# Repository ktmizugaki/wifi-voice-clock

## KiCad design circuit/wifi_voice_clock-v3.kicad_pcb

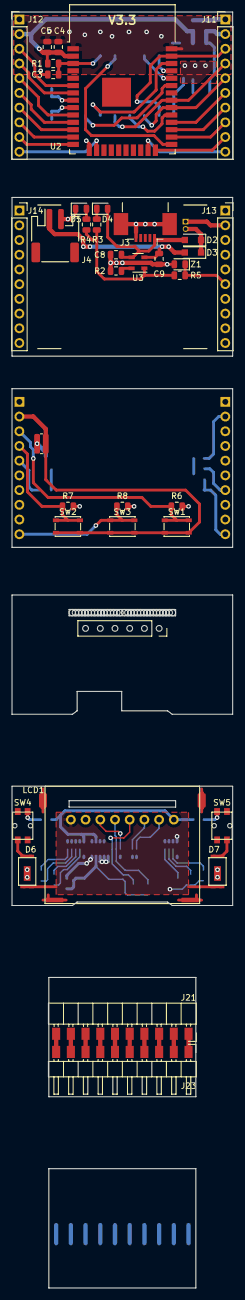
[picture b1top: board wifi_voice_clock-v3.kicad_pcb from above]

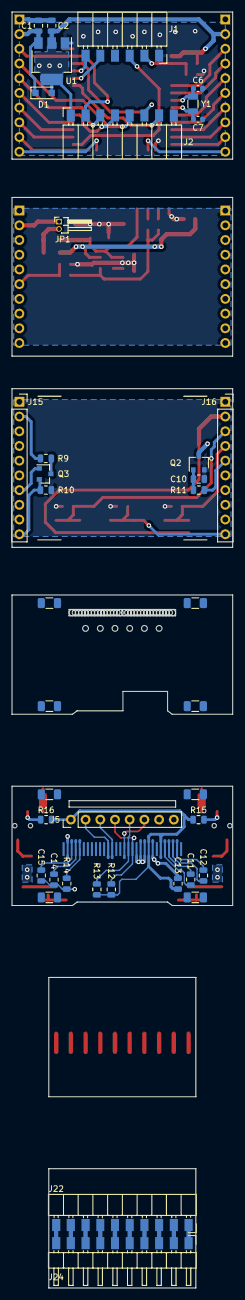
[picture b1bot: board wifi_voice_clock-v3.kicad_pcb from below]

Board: 2 copper layers, 38.1 x 220.3 mm, 68 parts (31 on the bottom side), 88 nets.

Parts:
C1, C2, C10, C11, C12, C13: 1uF; C_0805_2012Metric
C3, C4: 0.1uF; C_0805_2012Metric
C5, C8, C9: 10uF; C_0805_2012Metric
C6, C7: 15pF; C_0603_1608Metric
C14: 4.7uF; C_0805_2012Metric
C15: 2.2uF; C_0805_2012Metric
D1, D2: GS1010FL; D_SOD-123F
D3: SS2040FL; D_SOD-123F
D4: Orange; LED_0805_2012Metric
D5: Grean; LED_0805_2012Metric
D6, D7: SPMWHT541MD5WAR0SD; LM561B
J1: PinSocket 1x06 5.7mm; PinSocket_1x06_P2.54mm_5.7mm_Horizontal_SMD
J2: PinSocket 1x08 5.7mm; PinSocket_1x08_P2.54mm_5.7mm_Horizontal_SMD
J3: USB_B_Mini; USB_Mini-B_Hirose_UX60SC-MB-5ST
J4: BATTERY; JST_PH_S2B-PH-SM4-TB_1x02-1MP_P2.00mm_Horizontal
J5: PinHeader 1x08 7.7mm; PinHeader_1x08_P2.54mm_Vertical
J11, J12: PinHeader 1x10 7.7mm; PinHeader_1x10_P2.54mm_Vertical
J13, J14, J15, J16: PinSocket 1x10 3.5mm; PinSocket_1x10_P2.54mm_Vertical
J21, J22: PinSocket 1x10 3.5mm; PinSocket_1x10_P2.54mm_3.5mm_Horizontal_SMD
J23, J24: PinHeader 1x10 3mm; PinHeader_1x10_P2.54mm_3mm_Horizontal_SMD
JP1: Jumper; PinHeader_1x02_P1.27mm_Horizontal
LCD1: ER-OLED0.96; OLED0.96
LS1: CES-20134-088PM; R_0612_1632Metric
Q2: 2SC3265-Y; SC-59
Q3: BSS138; SOT-23
R1, R2, R5, R6, R7, R8, R10, R12, R13: 10K; R_0805_2012Metric
R3, R4: 470; R_0805_2012Metric
R9: 40K; R_0805_2012Metric
R11: 820; R_0805_2012Metric
R14: 910K; R_0805_2012Metric
R15, R16: 1K; R_0805_2012Metric
SW1, SW2, SW3: SW_Push; SW_SPST_PTS810
SW4, SW5: THAU13
U1: ADP3338AKCZ-3.3; SOT-223-3_TabPin2
U2: ESP32-WROOM-32D; ESP32-WROOM-32
U3: MCP73831-2-OT; SOT-23-5
Y1: FC-135; Crystal_SMD_3215-2Pin_3.2x1.5mm
Z1: 3.3V; D_0805_2012Metric

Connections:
+3V3: C2.1, C4.2, C5.2, D1.2, J2.1, J12.2, R1.2, U1.2, U2.2
+5V: C8.1, D2.2, D4.2, J3.1, U3.4
+BATT: C9.2, D3.2, J4.1, U3.3
/CHGR_GND: C8.2, C9.1, D5.1, J3.5, J3.6, J4.2, J13.1, J14.1, R2.1, U3.2, Z1.2
/CHGR_STAT: J13.6, R5.2, Z1.1
/CHGR_VCC: J13.2, JP1.1
/CPU_EN: C3.1, J1.2, R1.1, U2.3
/CPU_IO0: J1.3, U2.25
/CPU_IO2: J11.9, U2.24
/CPU_IO4: J11.8, U2.26
/CPU_IO12: J12.9, U2.14
/CPU_IO13: J12.10, U2.16
/CPU_IO14: J12.8, U2.13
/CPU_IO15: J11.10, U2.23
/CPU_IO16: J11.7, U2.27
/CPU_IO17: J11.6, U2.28
/CPU_IO27: J12.7, U2.12
/CPU_RXD0: J1.5, U2.34
/CPU_SPK: J12.5, U2.10
/CPU_SPK2: J12.6, U2.11
/CPU_SW1: J12.3, U2.6
/CPU_SW2: J12.4, U2.7
/CPU_TXD0: J1.6, U2.35
/CPU_VSPICLK: J2.3, J11.5, U2.30
/CPU_VSPICS0: J2.4, U2.29
/CPU_VSPID: J2.2, J11.3, U2.37
/CPU_VSPIHD: J2.7, U2.33
/CPU_VSPIQ: J2.5, J11.4, U2.31
/CPU_VSPIWP: J2.6, U2.36
/CTRL_3V3: J16.2, LS1.1, SW1.2, SW2.2, SW3.2
/CTRL_GND: C10.2, J15.1, J16.1, Q2.2, R6.1, R7.1, R8.1, R10.1
/CTRL_SPK: J16.5, R11.2
/CTRL_SW1: J16.3, R6.2, SW1.1
/CTRL_SW2: J16.4, R7.2, SW2.1
/CTRL_SW3: J16.10, R8.2, SW3.1
/CTRL_VCC: J15.2, R9.2
/CTRL_VMES: J15.10, Q3.2, R10.2
/CTRL_VOUT: J15.7, Q3.1
/LCD_3V3: C13.2, J5.1, LCD1.6, LCD1.9, R12.2, R13.2, R15.2, R16.2
/LCD_GND: C13.1, C14.2, C15.2, D6.1, D7.1, J5.8, LCD1.8, LCD1.10, LCD1.11, LCD1.12, LCD1.29, R14.2
/LCD_LCDRS: J5.6, LCD1.15
/LCD_SCLK: J5.3, LCD1.18
/LCD_SDI: J5.2, LCD1.19
/MCP73831_STAT: R3.1, R4.1, R5.1, U3.1
/~LCD_LCDCS: J5.4, LCD1.13, R12.1
/~LCD_LCDRST: J5.5, LCD1.14, R13.1
GND: C1.2, C2.2, C3.2, C4.1, C5.1, C6.1, C7.1, J1.1, J2.8, J11.1, J12.1, U1.1, U2.1, U2.15, U2.38
unnamed: C6.2, U2.8, Y1.1
unnamed: C7.2, U2.9, Y1.2
unnamed: C10.1, Q2.1, R11.1
unnamed: C11.1, LCD1.4
unnamed: C11.2, LCD1.5
unnamed: C12.1, LCD1.2
unnamed: C12.2, LCD1.3
unnamed: C14.1, LCD1.27
unnamed: C15.1, LCD1.28
unnamed: D2.1, D3.1, JP1.2
unnamed: D4.1, R3.2
unnamed: D5.2, R4.2
unnamed: D6.2, SW4.1
unnamed: D7.2, SW5.1
unnamed: J21.1, J23.1
unnamed: J21.2, J23.2
unnamed: J21.3, J23.3
unnamed: J21.4, J23.4
unnamed: J21.5, J23.5
unnamed: J21.6, J23.6
unnamed: J21.7, J23.7
unnamed: J21.8, J23.8
unnamed: J21.9, J23.9
unnamed: J21.10, J23.10
unnamed: J22.1, J24.1
unnamed: J22.2, J24.2
unnamed: J22.3, J24.3
unnamed: J22.4, J24.4
unnamed: J22.5, J24.5
unnamed: J22.6, J24.6
unnamed: J22.7, J24.7
unnamed: J22.8, J24.8
unnamed: J22.9, J24.9
unnamed: J22.10, J24.10
unnamed: LCD1.26, R14.1
unnamed: LS1.2, Q2.3
unnamed: Q3.3, R9.1
unnamed: R2.2, U3.5
unnamed: R15.1, SW4.2
unnamed: R16.1, SW5.2
VCC: C1.1, D1.1, J11.2, U1.3

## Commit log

2021-07-06 Add circuit and gerver
2021-07-07 Add prog skelton
2021-07-14 Encrypto nvs with pre generated key
2021-07-26 Add simple_wifi
2021-07-26 Add json_str
2021-07-26 stub http_wifi_conf
2021-07-26 Add kurukuru
2021-07-26 Add connect to wifi conf
2021-07-26 Add http_html_cmn
2021-07-26 Implement handle_initial
2021-07-26 Implement http_wifi_conf
2021-07-26 Try mobile friendly
2021-07-26 Add "Uploaded files and code to GitHub" log
2021-07-31 Fix password in simple_wifi
2021-07-31 Fix wifi conf does not check valid
2021-08-02 Change prefix of SSID
2021-08-09 Fix project name in cmake build
2021-08-28 Update instractions in hackaday
2021-08-30 Add lock to simple_wifi
2021-08-30 Add simple wifi event
2021-08-30 Add "OLED worked! at least once" log
2021-09-05 Add alarm conf
2021-09-14 Add switches
2021-09-17 Add clock and sync with ntp
2021-09-17 Add lan manager
    - Add function to connect to wifi using wifi_conf
    - Add function to get mode of simple_wifi
2021-09-20 Fix http_wifi_conf
2021-10-03 Move gen outside of Makefile
2021-10-03 compile only relevant sources
2021-10-03 Fix cmake build
2021-10-03 Introduce event based loop
2021-10-03 Add display and graphics
2021-10-03 Add display clock
2021-10-03 Show SSID and password
2021-10-03 Add font/lang tools
2021-10-03 Add bitmap and text
2021-10-03 Add ssd1306 driver
2021-10-03 Add shinonome fonts
2021-10-03 Use shinonome to display texts
2021-10-03 Rework wifi_conf
2021-10-06 Add power management and wakeup timer
2021-10-07 Add vcc
2021-10-09 Use cmn.api
2021-10-09 Add clock conf
2021-10-09 Add index html
    Also handle SIGPIPE in test http server. changing page sometimes cause this signal.
2021-10-14 Add suspend mode
2021-10-14 Implement auto sync
2021-10-16 Send vcc to syslog server
2021-10-16 Add use 32KHz crystal settings to defaults
    It is needed to flash bootloader with this config
2021-10-16 Add audio component
2021-10-23 Implement play alarm
    Also increase max alarm sound.
2021-10-23 Add "Implemented display" log
2021-10-24 Add spiffs
2021-10-24 Implement say time
2021-10-25 Check battery level before starting wifi
2021-11-07 Improve json_str document
2021-11-10 Document clock
2021-11-11 Document switches
2021-11-14 Document alarm
2021-11-14 Document wifi conf
2021-11-14 Document simple wifi
2021-11-20 Measure real input voltage
    Circuit is from https://jeelabs.org/2013/05/17/zero-powe-battery-measurement/
2021-11-23 Add "Add alarm functionality" log
2021-12-05 Add tests for cmn.js
    Using Mocha.js with Chai.js.
2021-12-05 Update http_html_cmn
    - Make send error json cmn
    - Decode urlencoded parameters in query parse.
    - Attempt to support larger body using less memory in query parse.
2021-12-05 Implement update firmware
2021-12-05 Implement update spiffs
2021-12-05 Add http_firmware
2021-12-05 Disable print time for release build
2021-12-12 Change hostname used in DHCP request
2021-12-19 Add callbacks to firmware update
2021-12-26 Show date by right button
2021-12-26 Add "Firmware update" log
2022-03-08 Swap function of middle click and middle long
2022-03-08 Show battery level on clock
2022-03-17 Implement listview and menu
2022-03-17 Add main menu
2022-03-30 Adjust OLED footprint
2022-05-02 Add "Battery voltage measurement" log
